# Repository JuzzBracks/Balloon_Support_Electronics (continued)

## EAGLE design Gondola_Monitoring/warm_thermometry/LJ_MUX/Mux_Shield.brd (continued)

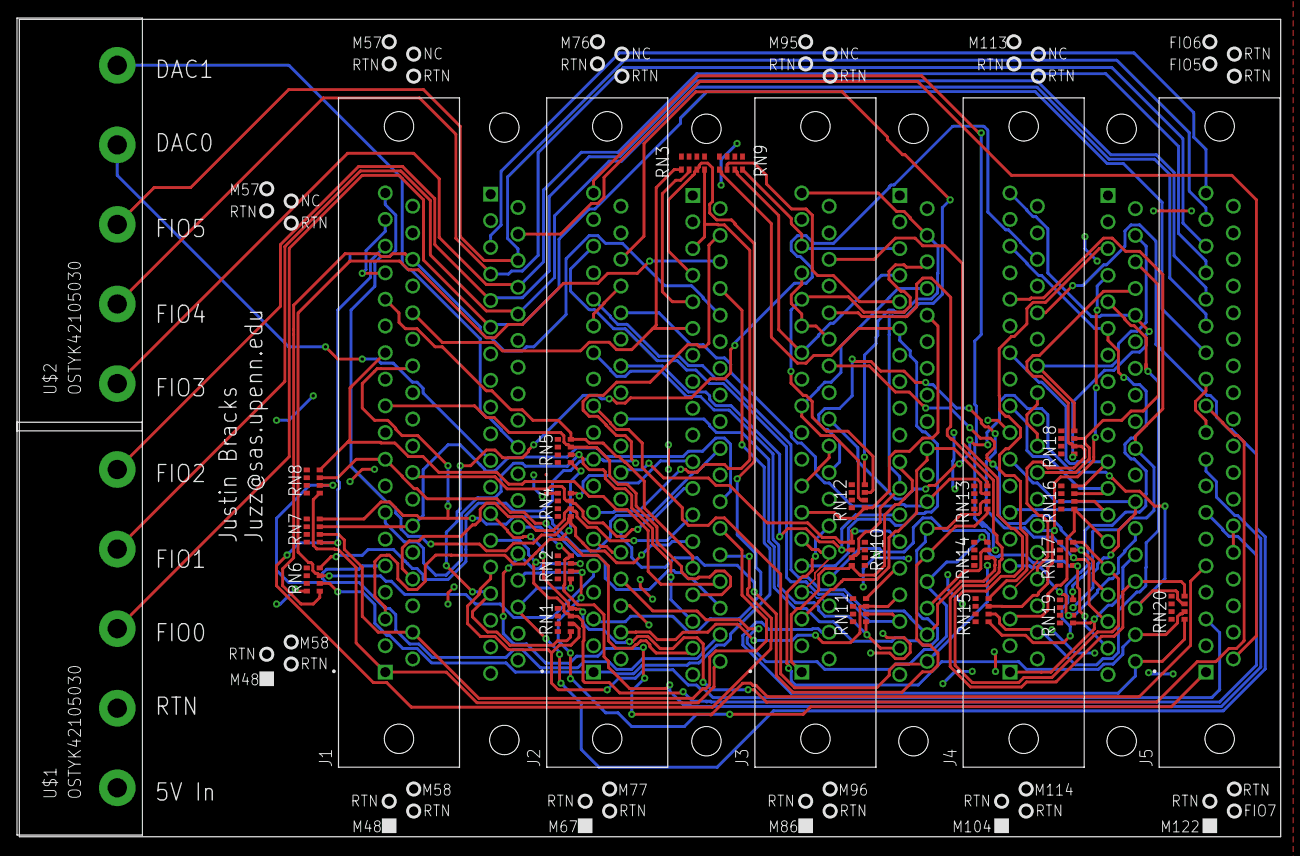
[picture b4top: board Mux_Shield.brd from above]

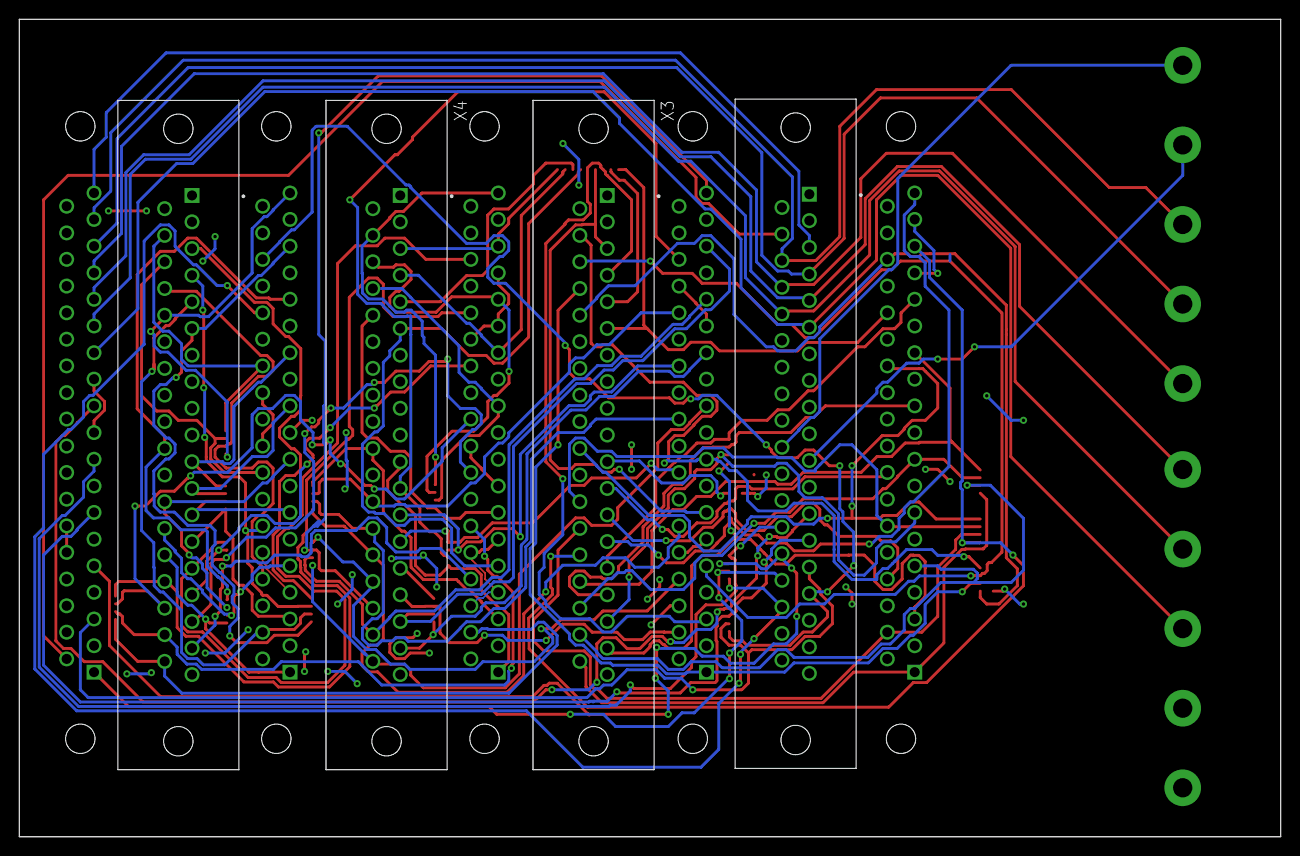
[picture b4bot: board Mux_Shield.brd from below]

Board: 2 copper layers, 130.8 x 84.8 mm, 31 parts (4 on the bottom side), 92 nets.

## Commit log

2024-11-11 Initial Commit
    Includes TIM PBoB, Warm Thermometry and BLAST PSS.
2025-03-19 The relay listed in the BoM was wrong
    in the name
